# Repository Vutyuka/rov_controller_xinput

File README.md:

# ROV Controller firmware

ROV Controller firmware, emulating an XBOX gamepad,
using XInput. An underwater casing will be used,
so all buttons are two-state push buttons.
Buttons represent Hall-effect sensors in the hardware.

Basic controller functionality, easy to add and remove buttons:

1. Add/remove pinout definition for pin.
2. Add/remove pin to button_table.
3. Change button_num.

Using Left Joystick with 4 push buttons. 
Joystick position/speed can be toggled by push button.

Any number of discrete speeds can be added to motor_speed_t.

Tested on Pro Micro(has to be flashed as Leonardo).

**To flash:** Press reset just as the IDE shows "Uploading" promt
IT WILL BRICK THE DEVICE IF THIS IS NOT DONE.

For more on XInput: https://github.com/dmadison/ArduinoXInput

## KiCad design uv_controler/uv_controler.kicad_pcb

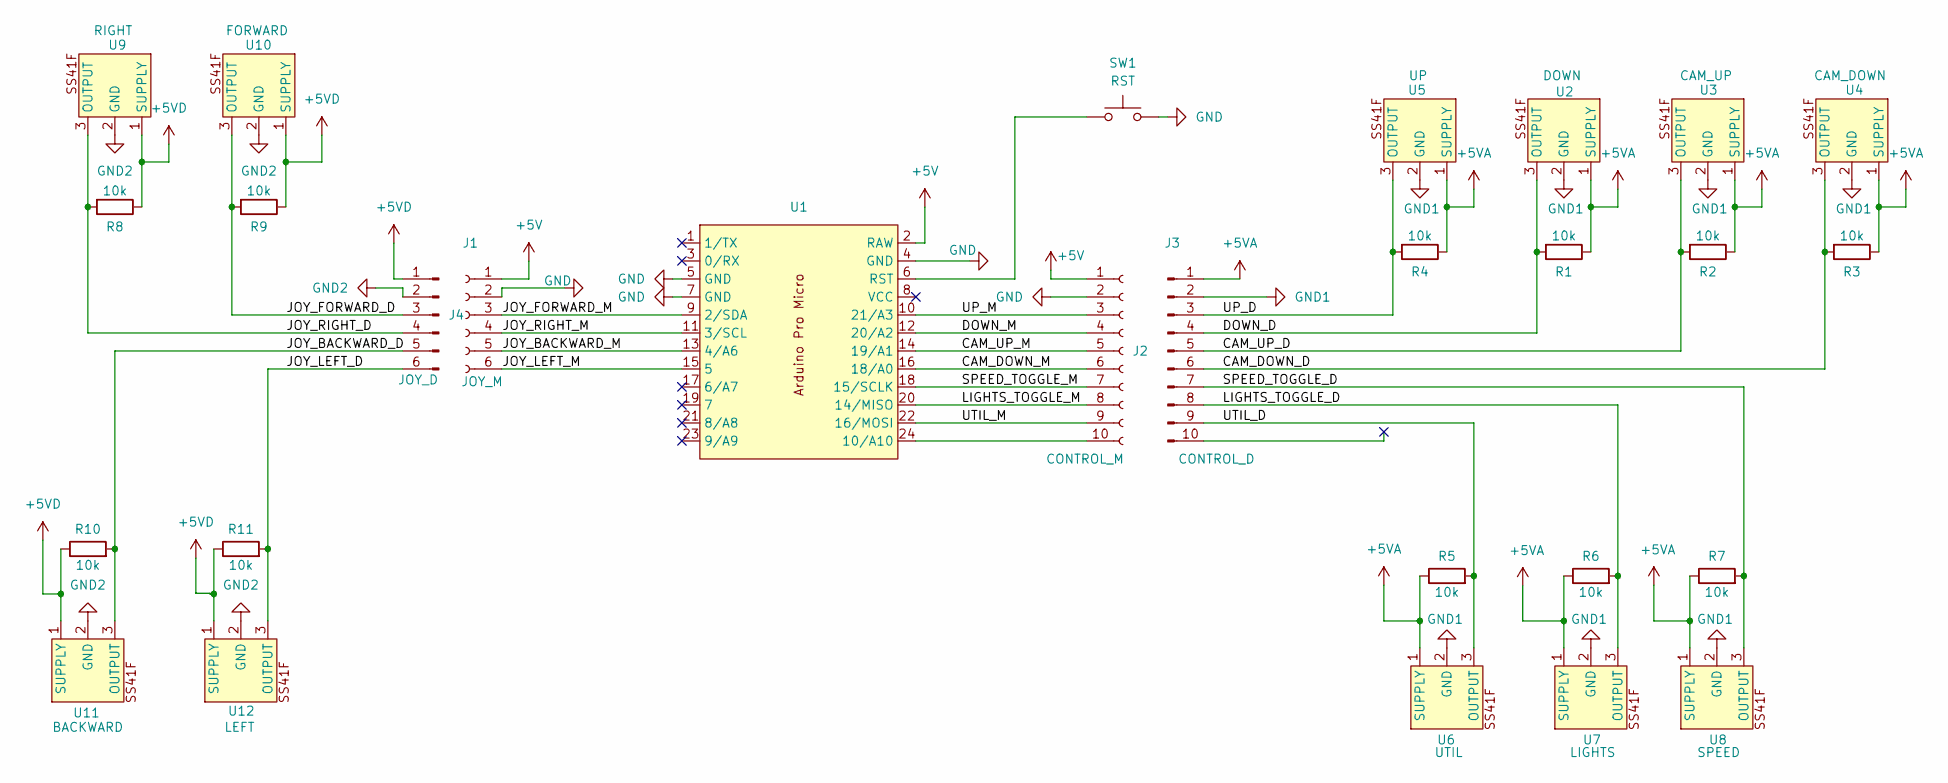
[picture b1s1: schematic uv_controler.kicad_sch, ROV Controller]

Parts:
J1: JOY_M; PinSocket_1x06_P2.54mm_Vertical
J2: CONTROL_M; PinSocket_1x10_P2.54mm_Vertical
J3: CONTROL_D; PinHeader_1x10_P2.54mm_Vertical
J4: JOY_D; PinHeader_1x06_P2.54mm_Vertical
R1, R2, R3, R4, R5, R6, R7, R8, R9, R10, R11: 10k; R_0603_1608Metric_Pad0.98x0.95mm_HandSolder
SW1: RST; SW_Tactile_SPST_Angled_PTS645Vx31-2LFS
U1: Arduino_Pro_Micro
U2: DOWN; SS41F
U3: CAM_UP; SS41F
U4: CAM_DOWN; SS41F
U5: UP; SS41F
U6: UTIL; SS41F
U7: LIGHTS; SS41F
U8: SPEED; SS41F
U9: RIGHT; SS41F
U10: FORWARD; SS41F
U11: BACKWARD; SS41F
U12: LEFT; SS41F

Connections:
+5V: J1.1, J2.1, U1.2 (RAW)
+5VA: J3.1, R1.1, R2.1, R3.1, R4.1, R5.1, R6.1, R7.1, U2.1 (SUPPLY), U3.1 (SUPPLY), U4.1 (SUPPLY), U5.1 (SUPPLY), U6.1 (SUPPLY), U7.1 (SUPPLY), U8.1 (SUPPLY)
+5VD: J4.1, R8.1, R9.1, R10.1, R11.1, U9.1 (SUPPLY), U10.1 (SUPPLY), U11.1 (SUPPLY), U12.1 (SUPPLY)
/CAM_DOWN_D: J3.6, R3.2, U4.3 (OUTPUT)
/CAM_DOWN_M: J2.6, U1.16 (18/A0)
/CAM_UP_D: J3.5, R2.2, U3.3 (OUTPUT)
/CAM_UP_M: J2.5, U1.14 (19/A1)
/DOWN_D: J3.4, R1.2, U2.3 (OUTPUT)
/DOWN_M: J2.4, U1.12 (20/A2)
/JOY_BACKWARD_D: J4.5, R10.2, U11.3 (OUTPUT)
/JOY_BACKWARD_M: J1.5, U1.13 (4/A6)
/JOY_FORWARD_D: J4.3, R9.2, U10.3 (OUTPUT)
/JOY_FORWARD_M: J1.3, U1.9 (2/SDA)
/JOY_LEFT_D: J4.6, R11.2, U12.3 (OUTPUT)
/JOY_LEFT_M: J1.6, U1.15 (5)
/JOY_RIGHT_D: J4.4, R8.2, U9.3 (OUTPUT)
/JOY_RIGHT_M: J1.4, U1.11 (3/SCL)
/LIGHTS_TOGGLE_D: J3.8, R6.2, U7.3 (OUTPUT)
/LIGHTS_TOGGLE_M: J2.8, U1.20 (14/MISO)
/SPEED_TOGGLE_D: J3.7, R7.2, U8.3 (OUTPUT)
/SPEED_TOGGLE_M: J2.7, U1.18 (15/SCLK)
/UP_D: J3.3, R4.2, U5.3 (OUTPUT)
/UP_M: J2.3, U1.10 (21/A3)
/UTIL_D: J3.9, R5.2, U6.3 (OUTPUT)
/UTIL_M: J2.9, U1.22 (16/MOSI)
GND: J1.2, J2.2, SW1.2, U1.4 (GND), U1.5 (GND), U1.7 (GND)
GND1: J3.2, U2.2 (GND), U3.2 (GND), U4.2 (GND), U5.2 (GND), U6.2 (GND), U7.2 (GND), U8.2 (GND)
GND2: J4.2, U9.2 (GND), U10.2 (GND), U11.2 (GND), U12.2 (GND)
unnamed: J2.10, U1.24 (10/A10)
unnamed: SW1.1, U1.6 (RST)

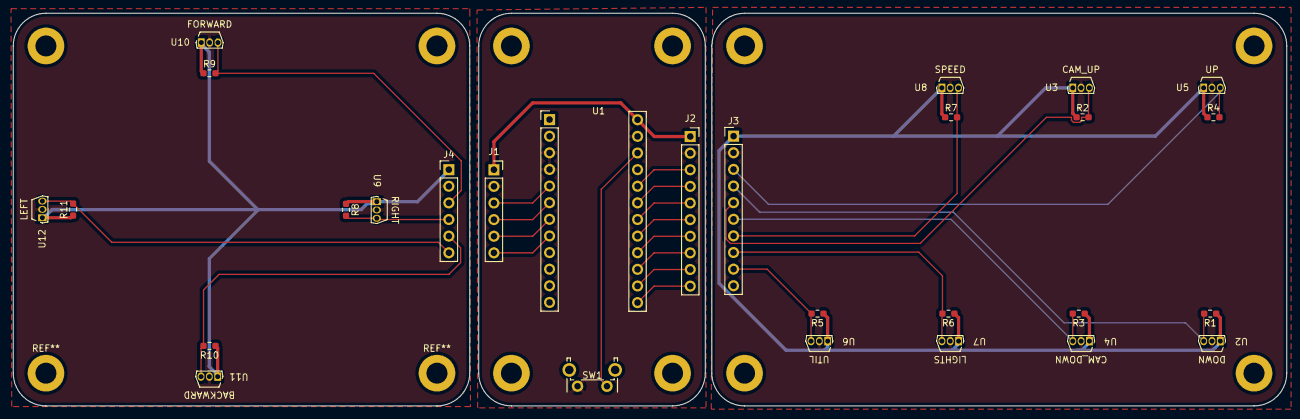
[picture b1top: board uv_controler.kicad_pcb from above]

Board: 2 copper layers, 194.6 x 60.0 mm, 28 parts (0 on the bottom side), 30 nets.

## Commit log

2023-03-22 naming restrictions
2023-06-18 discrete joystick added, untested probably not working
2023-06-24 discrete joystick finished with speed toggle
2025-03-16 added pcb, mapping added
2025-03-16 arranged pcb roughly
2025-04-26 pcb updates, lot of drc errors remain
2025-06-04 pcb cleanup june 6
2025-06-04 silk fix
